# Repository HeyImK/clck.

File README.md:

# clck.

A custom battery-powered alarm clock built for the [Hack Club BLARE](https://blare.hackclub.com/) program.

The goal of this project was simple: build an aesthetic alarm clock with a hint of brutalism style that doesn't use cheap rubber buttons. Instead, it uses four Cherry MX mechanical keyboard switches, a custom PCB, and a 3D printed enclosure. Everything is powered by a Wemos ESP32-C3 Mini, which handles the display, buttons,buzzer, etc. Btw Sponsored by Hack Club too!!!

## Overview

### Enclosure

| Front | Back |
|-------|------|
|  |  |

### PCB

| Front | Back |
|-------|------|
|  |  |

### Electronics

| Schematic | PCB Routing |
|-----------|-------------|
|  |  |

## Hardware

- Wemos ESP32-C3 Mini dev-board
- 2.25" SPI TFT display
- 4 Cherry MX mechanical switches
- Piezo buzzer
- Schottky diode (SS14)

The battery connects through a JST 2.0 connector and is charged using a external TP4056 module. 

## Pin Mapping

The ESP32-C3 Mini doesn't have many GPIOs, so every pin has been used by the display,buttons,buzzer etc.  

| Component | ESP32-C3 Pin(s) | Notes |
|-----------|-----------------|-------|
| Display (SPI) | GPIO4, GPIO6, GPIO7, GPIO2, GPIO10 | SCK, MOSI, CS, DC, RST |
| Piezo buzzer | GPIO8 | Connected to the positive terminal |
| Buttons | GPIO0, GPIO1, GPIO20, GPIO21 | Main control buttons |
| Battery input | VBUS |Connect to a charging module first |

## Assembly

The switch plate is designed around a thickness of **1.5 mm**. Making it thicker will prevent the Cherry MX switches from snapping into place correctly.

Before connecting the battery check the battery polarity.

## License

CERN-OHL-S-2.0 license

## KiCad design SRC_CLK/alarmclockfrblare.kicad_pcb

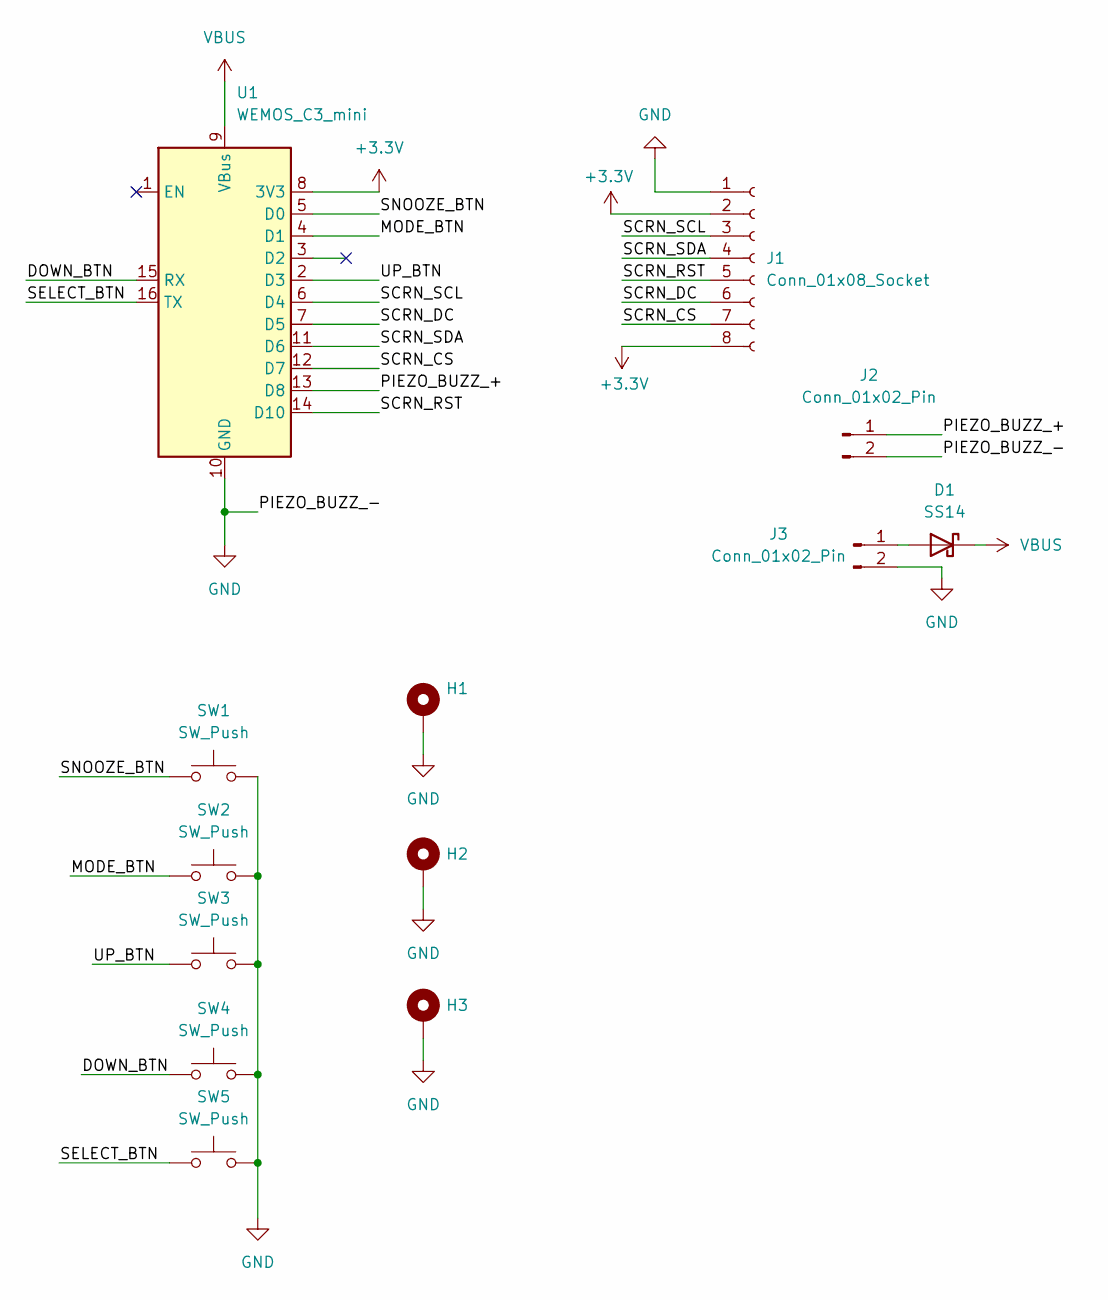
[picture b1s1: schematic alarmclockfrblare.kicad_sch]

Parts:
D1: SS14; D_SMA
H1, H2, H3: MountingHole_Pad; MountingHole_2.2mm_M2_Pad
J1: Conn_01x08_Socket; PinHeader_1x08_P2.54mm_Vertical
J2, J3: Conn_01x02_Pin; JST_PH_B2B-PH-K_1x02_P2.00mm_Vertical
SW1, SW2, SW3, SW4, SW5: SW_Push; SW_MX_1u
U1: WEMOS_C3_mini

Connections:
+3.3V: J1.2, J1.8, U1.8 (3V3)
/DOWN_BTN: SW4.1, U1.15 (RX)
/MODE_BTN: SW2.1, U1.4 (D1)
/PIEZO_BUZZ_+: J2.1, U1.13 (D8)
/SCRN_CS: J1.7, U1.12 (D7)
/SCRN_DC: J1.6, U1.7 (D5)
/SCRN_RST: J1.5, U1.14 (D10)
/SCRN_SCL: J1.3, U1.6 (D4)
/SCRN_SDA: J1.4, U1.11 (D6)
/SELECT_BTN: SW5.1, U1.16 (TX)
/SNOOZE_BTN: SW1.1, U1.5 (D0)
/UP_BTN: SW3.1, U1.2 (D3)
GND: H1.1 (1_1), H2.1 (1_1), H3.1 (1_1), J1.1, J2.2, J3.2, SW1.2, SW2.2, SW3.2, SW4.2, SW5.2, U1.10 (GND)
unnamed: D1.2 (A), J3.1
VBUS: D1.1 (K), U1.9 (VBus)

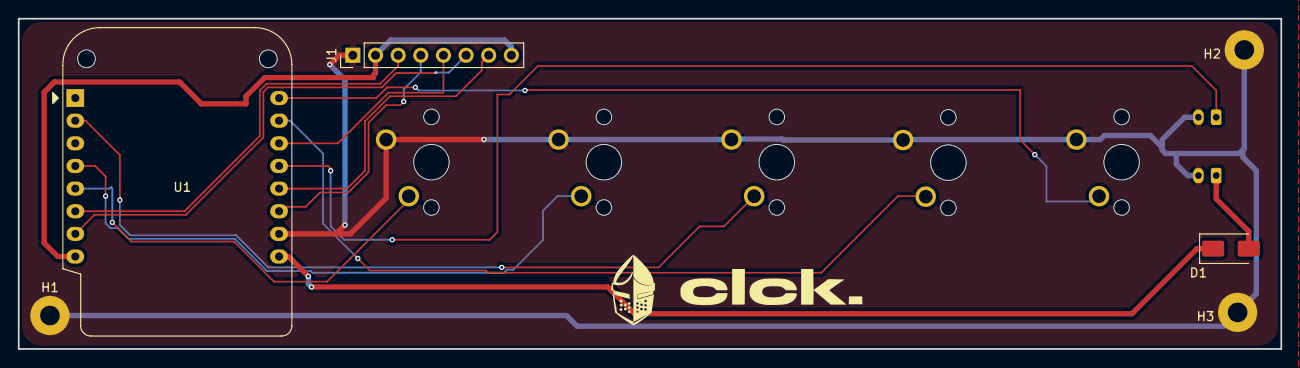
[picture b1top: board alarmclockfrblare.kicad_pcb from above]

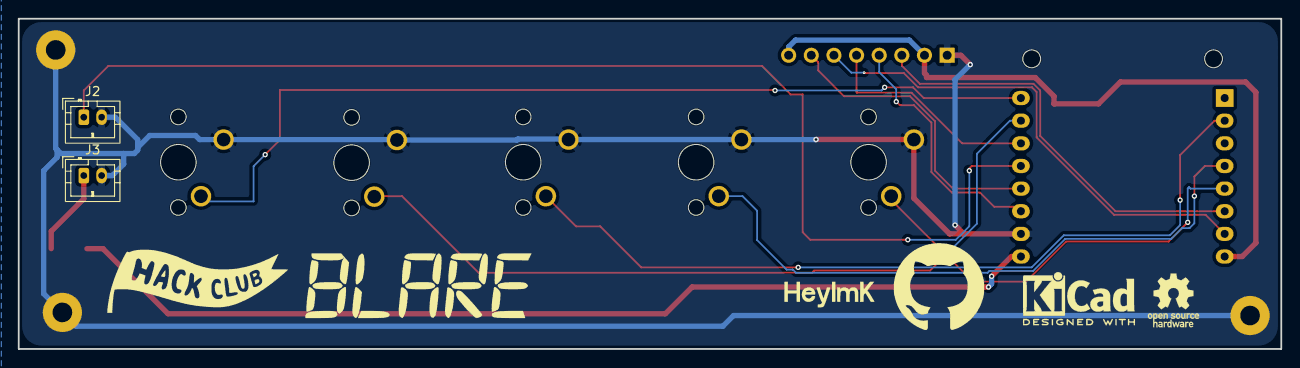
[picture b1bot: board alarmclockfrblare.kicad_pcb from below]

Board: 2 copper layers, 141.7 x 37.1 mm, 13 parts (2 on the bottom side), 15 nets.
